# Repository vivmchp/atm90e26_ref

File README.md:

# ATM90E26A Evaluation Board

KiCad 10.0 design for a single-phase energy metering evaluation board based on the Microchip ATM90E26A IC.

| Front | Back |
|:-----:|:----:|
|  |  |

## Features

- **ATM90E26A** high-precision energy metering IC (SSOP-28)
- **HLK-10M12** AC/DC power module (100-240VAC input, 12VDC/10W output)
- **ZMPT101K** voltage transformer (1000:1000) for isolated AC voltage sensing
- **MIC5209-3.3YS-TR** LDO for 3.3V power supply
- **24C02C** I2C EEPROM for calibration data storage
- **10D561** varistor for surge protection
- 10-pin header for MCU interface (SPI + I2C)
- Single-phase two-wire or three-wire configuration support

## Block Diagram

## Connectors

### AC Input (J1)
| Pin | Signal | Description |
|-----|--------|-------------|
| 1 | LINE | AC Live (100-240VAC) |
| 2 | NEUT | AC Neutral |

### Current Input (J2)
| Pin | Signal | Description |
|-----|--------|-------------|
| 1 | I1P | Current channel positive |
| 2 | I1N | Current channel negative |

### MCU Interface (J5)
| Pin | Signal | Description |
|-----|--------|-------------|
| 1 | +3.3V | 3.3V power output |
| 2 | GND | Ground |
| 3 | ATM_SDI | SPI data in (MOSI to ATM90E26) |
| 4 | ATM_SDO | SPI data out (MISO from ATM90E26) |
| 5 | ATM_CLK | SPI clock |
| 6 | ATM_CS | Chip select (active low) |
| 7 | ATM_IRQ | Interrupt output |
| 8 | ATM_CF1 | Energy pulse output |
| 9 | SCL | I2C clock (1K pull-up) |
| 10 | SDA | I2C data (1K pull-up) |

## PCB Specifications

| Parameter | Value |
|-----------|-------|
| Board size | 80mm × 70mm |
| Layers | 2 (Top + Bottom copper) |
| Thickness | 1.6mm |
| Default track | 0.2mm |
| Default via | 0.6mm / 0.3mm drill |
| HV track | 1.0mm |
| HV clearance | 1.0mm |

## Bill of Materials

| Ref | Part | Value | Package |
|-----|------|-------|---------|
| U1 | HLK-10M12 | 12V/10W | Module |
| U2 | ATM90E26-YU | - | SSOP-28 |
| U3 | MIC5209-3.3YS-TR | 3.3V | SOT-223 |
| U4 | 24C02C | 2Kbit | SOIC-8 |
| TR1 | ZMPT101K | 1000:1000 | Through-hole |
| Y1 | Crystal | 8.192MHz | HC49-U |
| RV1 | Varistor | 10D561 | Disc |
| R1 | Resistor | 200K/3W | Axial |
| C13, C14 | Capacitor | 12pF | 0603 |

## Manufacturing Files

Gerber files for PCB fabrication are in `ATM90E26_EVAL/output/`:

| File | Description |
|------|-------------|
| *-F_Cu.gbr | Front copper layer |
| *-B_Cu.gbr | Back copper layer |
| *-F_Mask.gbr | Front solder mask |
| *-B_Mask.gbr | Back solder mask |
| *-F_Paste.gbr | Front solder paste |
| *-B_Paste.gbr | Back solder paste |
| *-F_Silkscreen.gbr | Front silkscreen |
| *-B_Silkscreen.gbr | Back silkscreen |
| *-Edge_Cuts.gbr | Board outline |
| *-PTH.drl | Plated through holes |
| *-NPTH.drl | Non-plated holes |

## Requirements

- KiCad 10.0 or later

## License

Reference design for evaluation purposes.

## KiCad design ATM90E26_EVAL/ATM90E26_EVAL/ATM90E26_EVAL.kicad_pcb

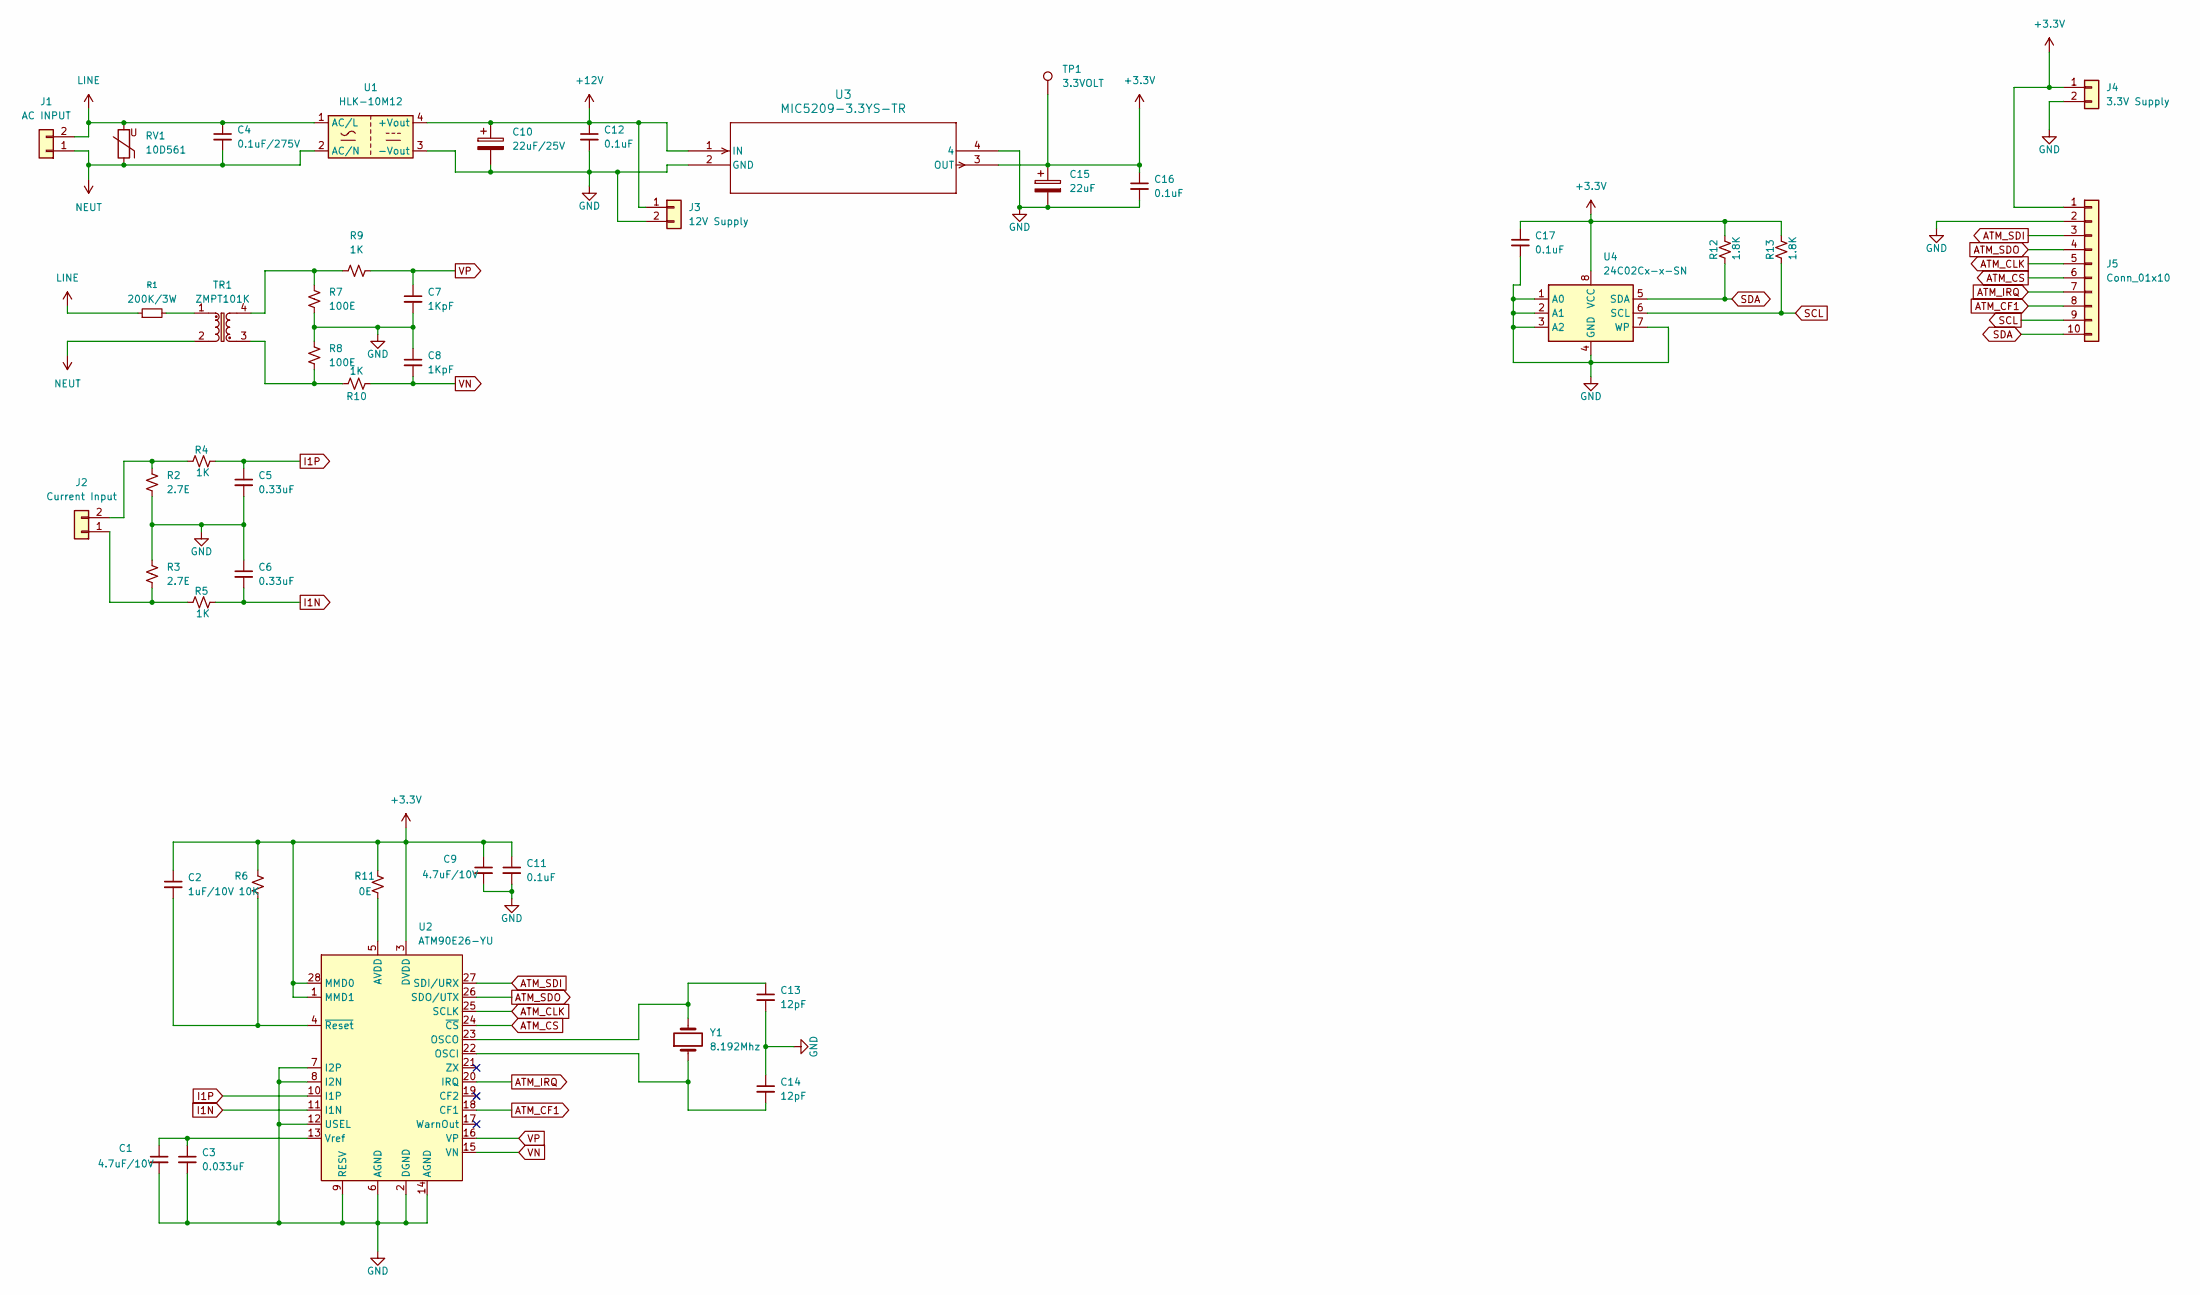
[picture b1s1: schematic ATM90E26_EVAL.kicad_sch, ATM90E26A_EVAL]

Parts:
C1, C9: 4.7uF/10V; C_0805_2012Metric
C2: 1uF/10V; C_0805_2012Metric
C3: 0.033uF; C_0603_1608Metric
C4: 0.1uF/275V; C_Rect_L16.5mm_W10.9mm_P15.00mm_MKT
C5, C6: 0.33uF; C_0603_1608Metric
C7, C8: 1KpF; C_0603_1608Metric
C10: 22uF/25V; CP_Radial_D5.0mm_P2.00mm
C11, C12, C16, C17: 0.1uF; C_0603_1608Metric
C13, C14: 12pF; C_0603_1608Metric
C15: 22uF; CP_EIA-3528-12_Kemet-T
J1: AC INPUT; TerminalBlock_Philmore_TB132_1x02_P5.00mm_Horizontal
J2: Current Input; TerminalBlock_Philmore_TB132_1x02_P5.00mm_Horizontal
J3: 12V Supply; PinHeader_1x02_P2.54mm_Vertical
J4: 3.3V Supply; PinHeader_1x02_P2.54mm_Vertical
J5: Conn_01x10; PinHeader_1x10_P2.54mm_Vertical
R1: 200K/3W; R_Axial_DIN0918_L18.0mm_D9.0mm_P22.86mm_Horizontal
R2, R3: 2.7E; R_0805_2012Metric
R4, R5, R9, R10: 1K; R_0805_2012Metric
R6: 10K; R_0805_2012Metric
R7, R8: 100E; R_0805_2012Metric
R11: 0E; R_0805_2012Metric
R12, R13: 1.8K; R_0805_2012Metric
RV1: 10D561; RV_Disc_D12mm_W3.9mm_P7.5mm
TP1: 3.3VOLT; TestPoint_THTPad_D1.0mm_Drill0.5mm
TR1: ZMPT101K; Transformer_Zeming_ZMPT101K
U1: HLK-10M12; Converter_ACDC_Hi-Link_HLK-10Mxx
U2: ATM90E26-YU; SSOP-28_5.3x10.2mm_P0.65mm
U3: MIC5209-3.3YS-TR; SOT-223
U4: 24C02Cx-x-SN; SOIC-8_3.9x4.9mm_P1.27mm
Y1: 8.192Mhz; Crystal_HC49-U_Vertical

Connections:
+3.3V: C2.1, C9.1, C11.1, C15.1, C16.1, C17.1, J4.1, J5.1, R6.1, R11.1, R12.1, R13.1, TP1.1 (1_1), U2.1 (MMD1), U2.3 (DVDD), U2.28 (MMD0), U3.3 (OUT), U4.8 (VCC)
+12V: C10.1, C12.1, J3.1, U1.4 (+Vout), U3.1 (IN)
ATM_CF1: J5.8, U2.18 (CF1)
ATM_CLK: J5.5, U2.25 (SCLK)
ATM_CS: J5.6, U2.24 (~CS)
ATM_IRQ: J5.7, U2.20 (IRQ)
ATM_SDI: J5.3, U2.27 (SDI/URX)
ATM_SDO: J5.4, U2.26 (SDO/UTX)
GND: C1.2, C3.2, C5.2, C6.1, C7.2, C8.1, C9.2, C10.2, C11.2, C12.2, C13.2, C14.1, C15.2, C16.2, C17.2, J3.2, J4.2, J5.2, R2.1, R3.2, R7.1, R8.2, U1.3 (-Vout), U2.2 (DGND), U2.6 (AGND), U2.7 (I2P), U2.8 (I2N), U2.9 (DGND), U2.12 (USEL), U2.14 (AGND), U3.2 (GND), U3.4, U4.1 (A0), U4.2 (A1), U4.3 (A2), U4.4 (GND), U4.7 (WP)
I1N: C6.2, R5.1, U2.11 (I1N)
I1P: C5.1, R4.1, U2.10 (I1P)
LINE: C4.1, J1.2, R1.1, RV1.2, U1.1 (AC/L)
NEUT: C4.2, J1.1, RV1.1, TR1.2, U1.2 (AC/N)
unnamed: J2.1, R3.1, R5.2
unnamed: J2.2, R2.2, R4.2
unnamed: R1.2, TR1.1
unnamed: R7.2, R9.2, TR1.4
unnamed: R8.1, R10.2, TR1.3
unnamed: R11.2, U2.5 (AVDD)
unnamed: C14.2, U2.22 (OSCI), Y1.1
unnamed: C13.1, U2.23 (OSCO), Y1.2
unnamed: C1.1, C3.1, U2.13 (Vref)
unnamed: C2.2, R6.2, U2.4 (~Reset)
SCL: J5.9, R13.2, U4.6 (SCL)
SDA: J5.10, R12.2, U4.5 (SDA)
VN: C8.2, R10.1, U2.15 (VN)
VP: C7.1, R9.1, U2.16 (VP)

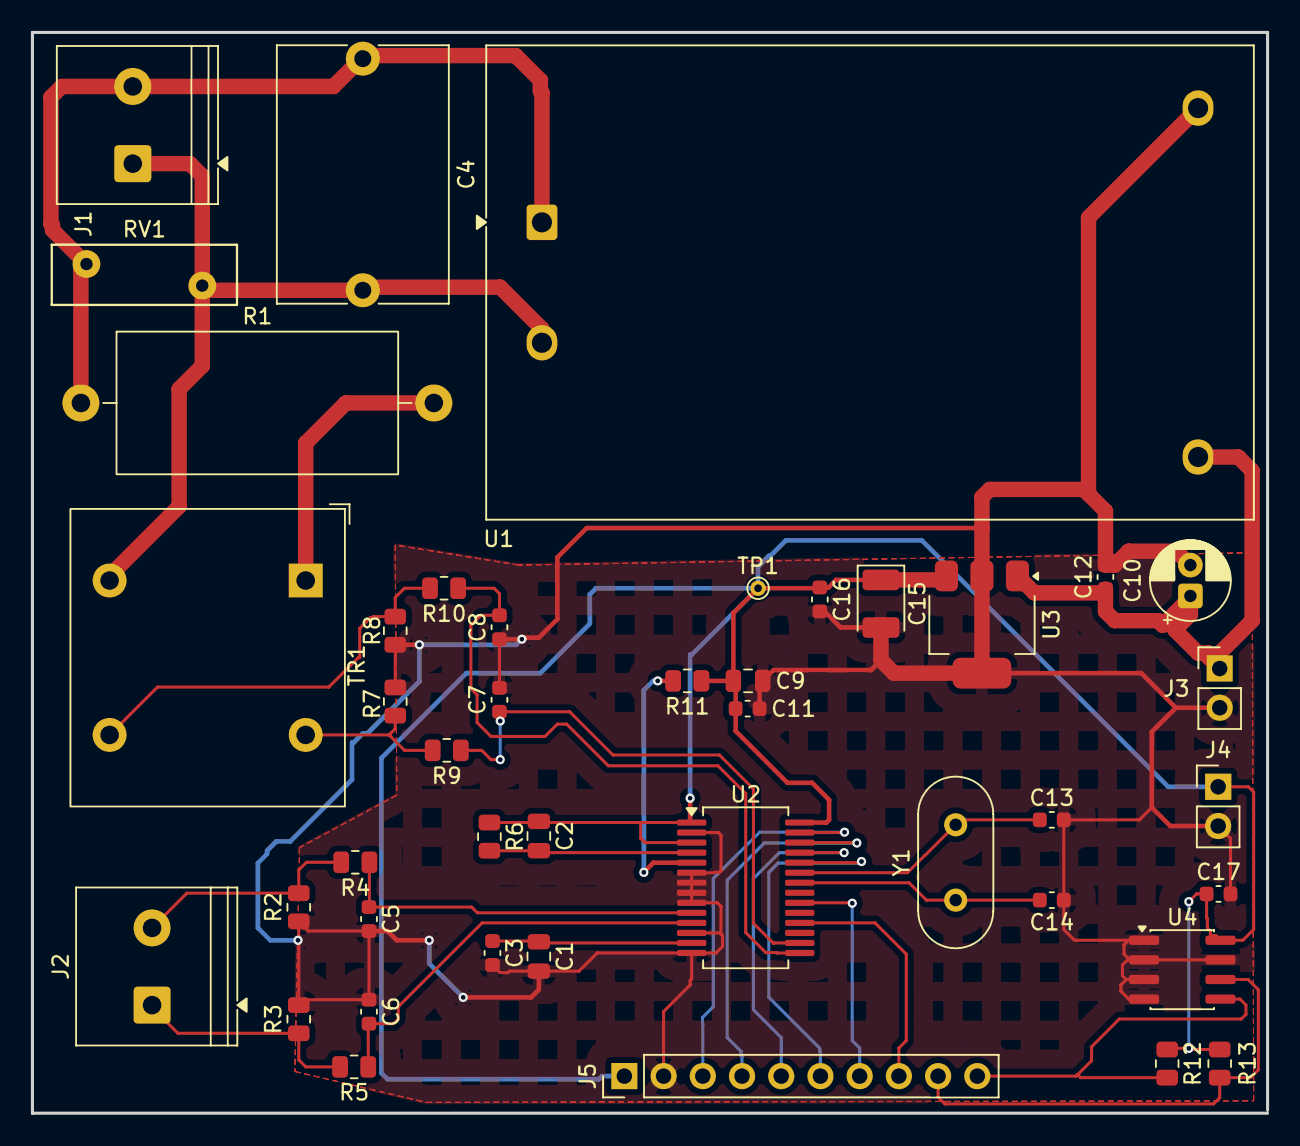
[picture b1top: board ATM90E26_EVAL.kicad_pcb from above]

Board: 2 copper layers, 80.0 x 70.0 mm, 43 parts (0 on the bottom side), 27 nets.
